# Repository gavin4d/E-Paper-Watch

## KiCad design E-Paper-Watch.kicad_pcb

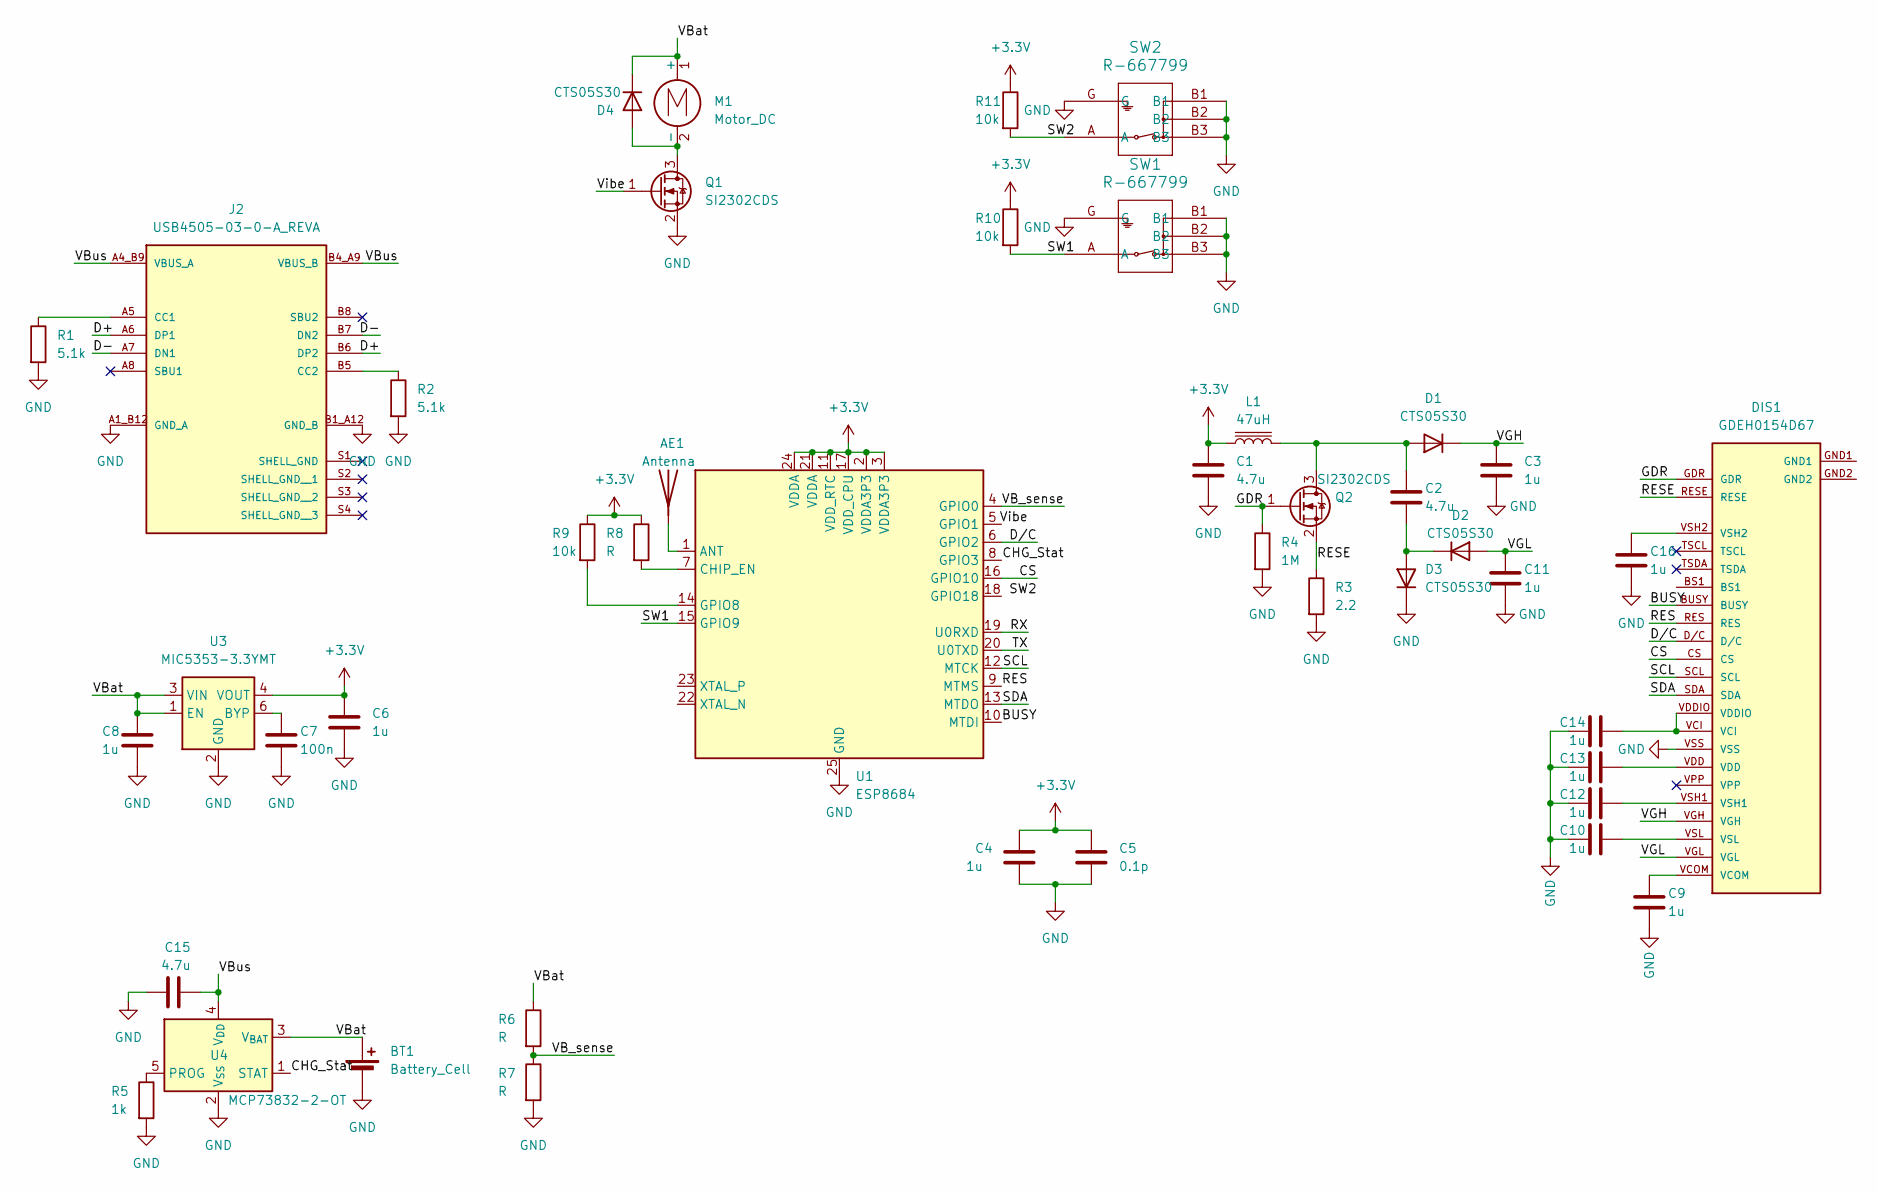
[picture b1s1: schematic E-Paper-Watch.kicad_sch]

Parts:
AE1: Antenna
BT1: Battery_Cell
C1, C2, C15: 4.7u; C_0805_2012Metric
C3, C4, C6, C8, C9, C10, C11, C12, C13, C14, C16: 1u; C_0805_2012Metric
C5: 0.1p; C_0805_2012Metric
C7: 100n; C_0805_2012Metric
D1, D2, D3, D4: CTS05S30; D_SOD-882
DIS1: GDEH0154D67
J2: USB4505-03-0-A_REVA; GCT_USB4505-03-0-A_REVA; PARTREV A
L1: 47uH; L_Bourns-SRN4018
M1: Motor_DC; Coin_Vibration_Motor_VC0824K001L
Q1, Q2: SI2302CDS; SOT-23
R1, R2: 5.1k; R_0805_2012Metric
R3: 2.2; R_0805_2012Metric
R4: 1M; R_0805_2012Metric
R5: 1k; R_0805_2012Metric
R6, R7, R8: R; R_0805_2012Metric
R9, R10, R11: 10k; R_0805_2012Metric
SW1, SW2: R-667799; R-667799_MIT
U1: ESP8684; QFN-24-1EP_4x4mm_P0.5mm_EP2.8x2.8mm
U3: MIC5353-3.3YMT; MLF-6-1EP_1.6x1.6mm_P0.5mm_EP0.5x1.26mm
U4: MCP73832-2-OT; SOT-23-5

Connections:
+3.3V: C1.1, C4.1, C5.1, C6.1, L1.1, R8.1, R9.1, R10.1, R11.1, U1.2 (VDDA3P3), U1.3 (VDDA3P3), U1.11 (VDD_RTC), U1.17 (VDD_CPU), U1.21 (VDDA), U1.24 (VDDA), U3.4 (VOUT)
/BUSY: DIS1.BUSY
/CHG_Stat: U4.1 (STAT)
/CS: DIS1.CS, U1.16 (GPIO10)
/D+: J2.A6 (DP1), J2.B6 (DP2)
/D-: J2.A7 (DN1), J2.B7 (DN2)
/D/C: DIS1.D/C, U1.6 (GPIO2)
/GDR: DIS1.GDR, Q2.1 (G), R4.1
/RES: DIS1.RES
/RESE: DIS1.RESE, Q2.2 (S), R3.1
/RX: U1.19 (U0RXD)
/SCL: DIS1.SCL, U1.12 (MTCK)
/SDA: DIS1.SDA, U1.13 (MTDO)
/SW1: R10.2, SW1.A, U1.15 (GPIO9)
/SW2: R11.2, SW2.A
/TX: U1.20 (U0TXD)
/VB_sense: R6.2, R7.1, U1.4 (GPIO0)
/VBat: BT1.1 (+), C8.1, D4.1 (K), M1.1 (+), R6.1, U3.1 (EN), U3.3 (VIN), U4.3 (V_{BAT})
/VBus: C15.2, J2.A4_B9 (VBUS_A), J2.B4_A9 (VBUS_B), U4.4 (V_{DD})
/VGH: C3.1, D1.1 (K), DIS1.VGH
/VGL: C11.1, D2.2 (A), DIS1.VGL
/Vibe: Q1.1 (G)
GND: BT1.2 (-), C1.2, C3.2, C4.2, C5.2, C6.2, C7.2, C8.2, C9.2, C10.1, C11.2, C12.1, C13.1, C14.1, C15.1, C16.2, D3.1 (K), DIS1.VSS, J2.A1_B12 (GND_A), J2.B1_A12 (GND_B), Q1.2 (S), R1.2, R2.2, R3.2, R4.2, R5.2, R7.2, SW1.B1, SW1.B2, SW1.B3, SW1.G, SW2.B1, SW2.B2, SW2.B3, SW2.G, U1.25 (GND), U3.2 (GND), U3.7 (GND), U4.2 (V_{SS})
unnamed: AE1.1, U1.1 (ANT)
unnamed: C9.1, DIS1.VCOM
unnamed: C10.2, DIS1.VSL
unnamed: C12.2, DIS1.VSH1
unnamed: C13.2, DIS1.VDD
unnamed: C14.2, DIS1.VCI, DIS1.VDDIO
unnamed: C16.1, DIS1.VSH2
unnamed: C2.1, D1.2 (A), L1.2, Q2.3 (D)
unnamed: C2.2, D2.1 (K), D3.2 (A)
unnamed: D4.2 (A), M1.2 (-), Q1.3 (D)
unnamed: J2.A5 (CC1), R1.1
unnamed: J2.B5 (CC2), R2.1
unnamed: R8.2, U1.7 (CHIP_EN)
unnamed: R9.2, U1.14 (GPIO8)
unnamed: C7.1, U3.6 (BYP)
unnamed: R5.1, U4.5 (PROG)

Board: 2 copper layers, 42 parts (0 on the bottom side), 32 nets, no tracks yet.
